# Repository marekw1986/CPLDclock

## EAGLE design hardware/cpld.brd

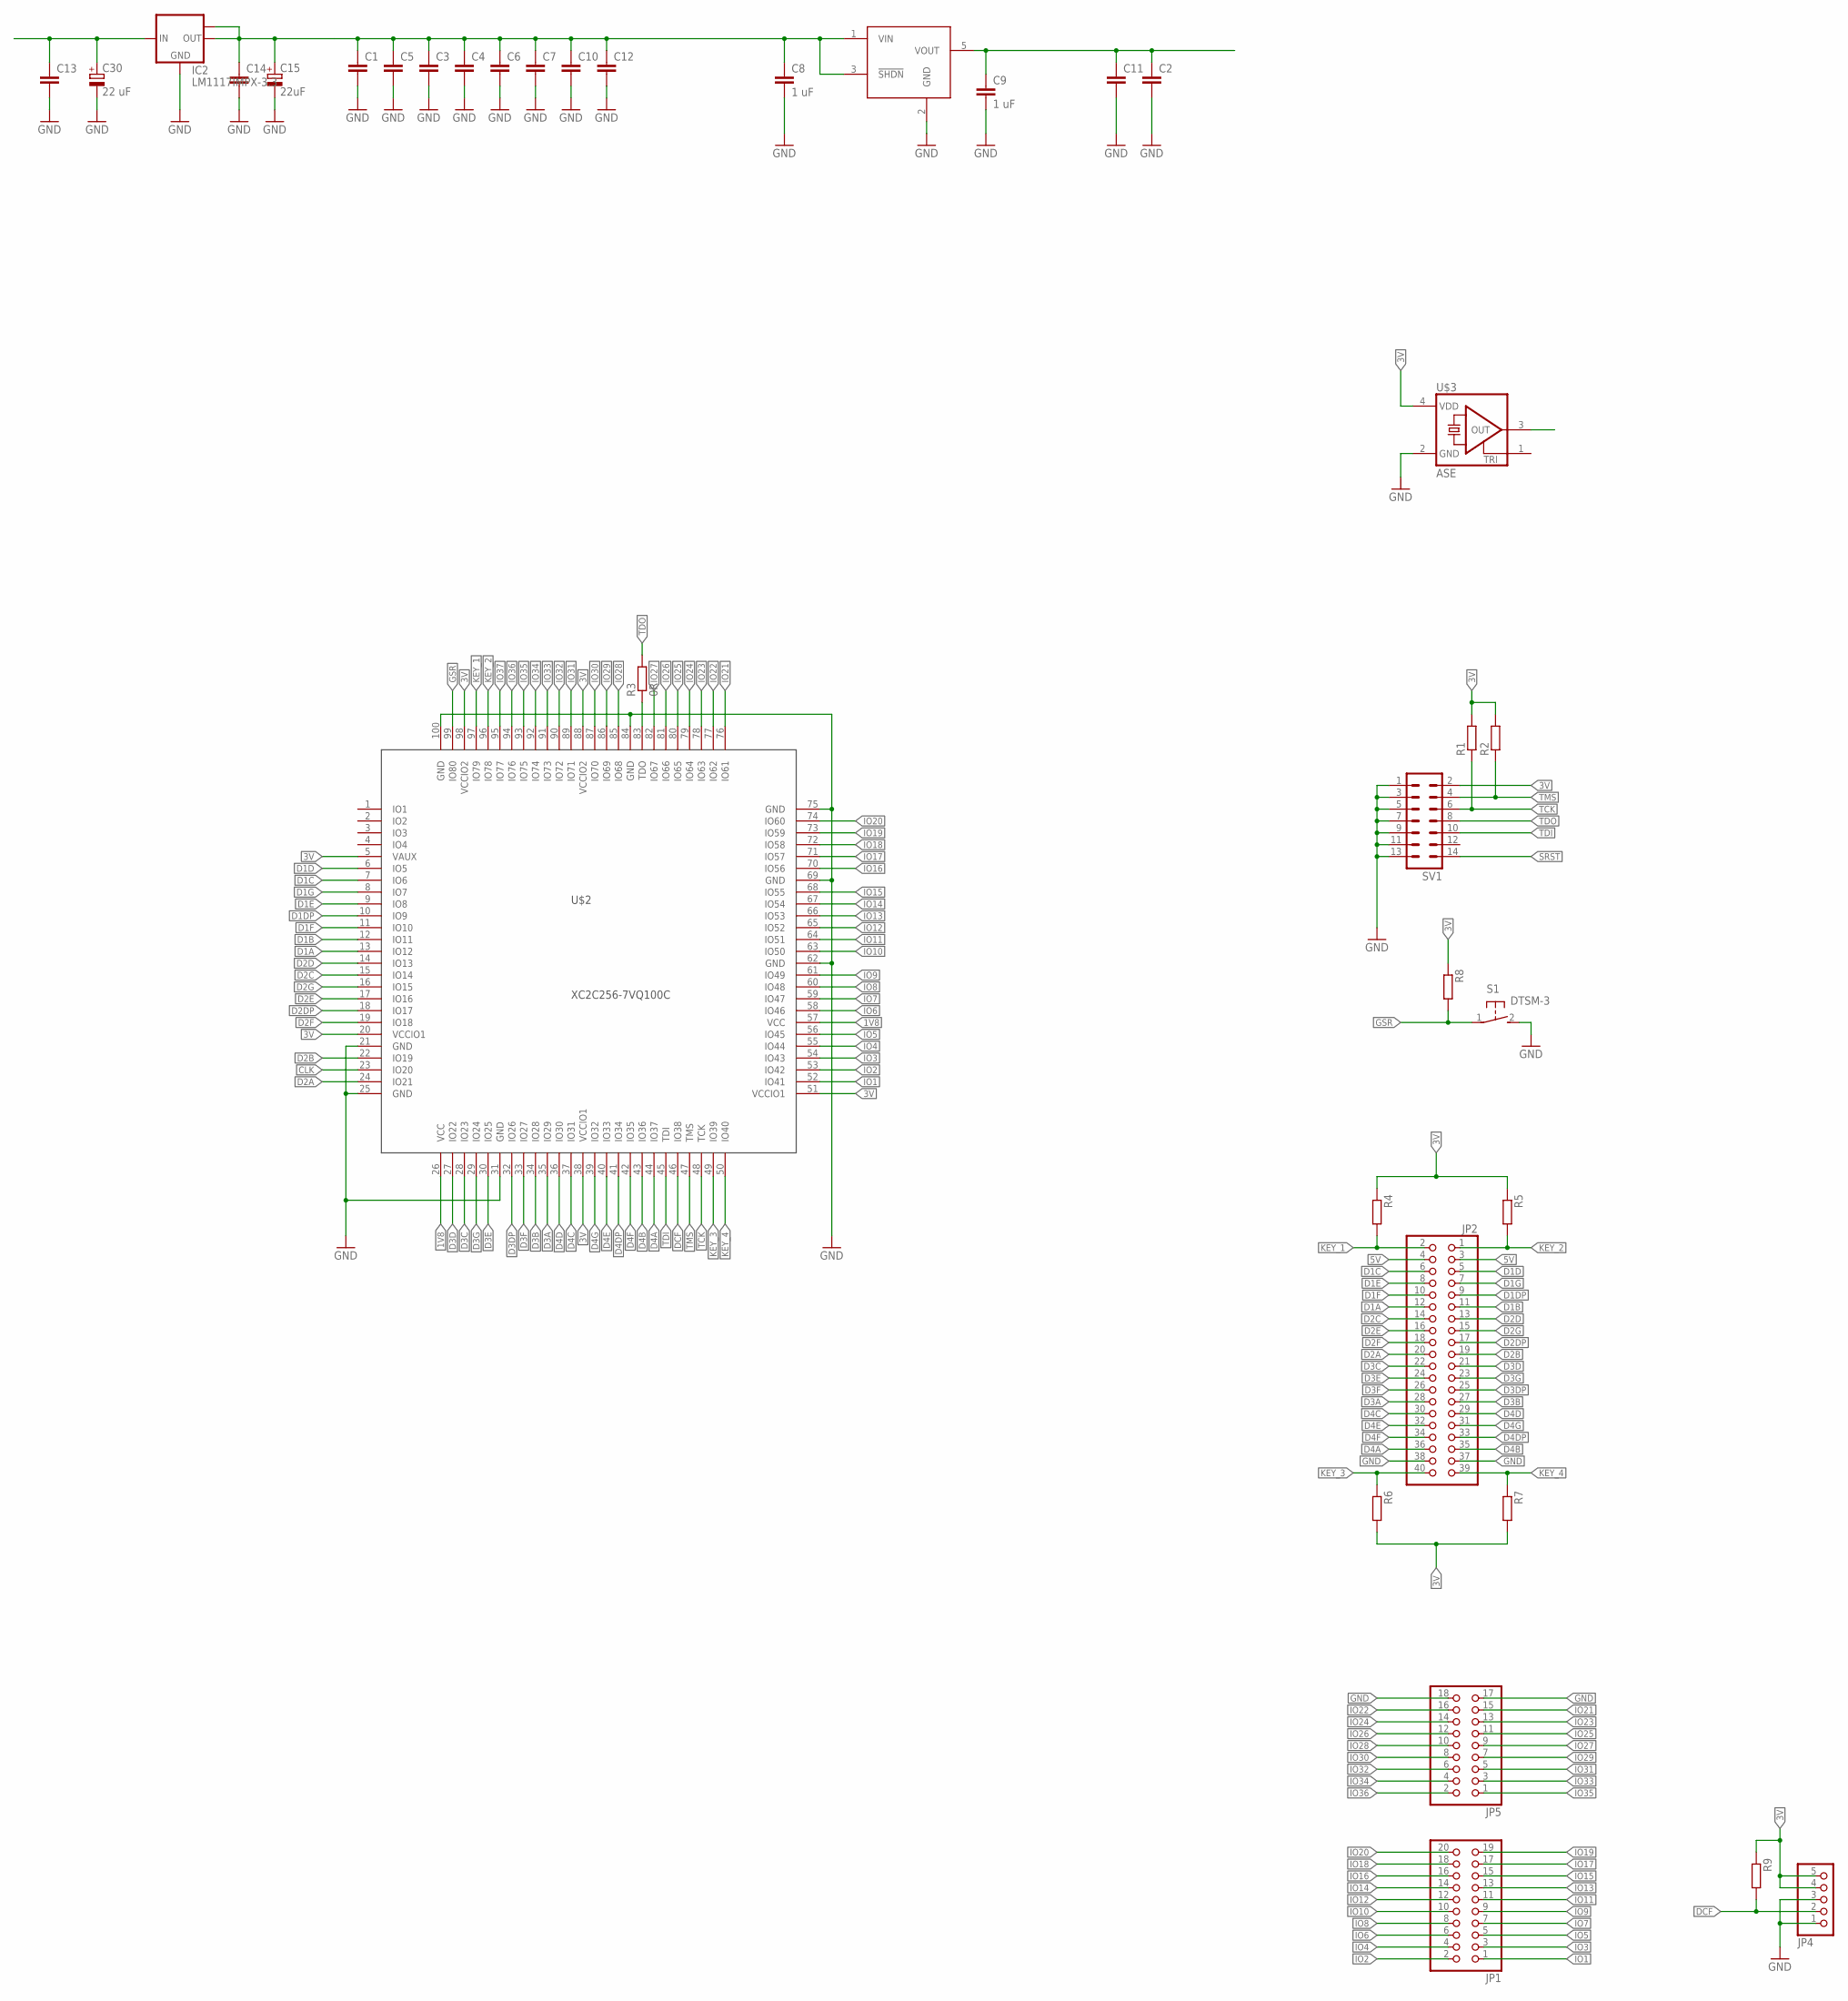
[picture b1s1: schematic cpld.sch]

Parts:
C1, C2, C4, C5, C7, C10, C11, C12, C13, C14: C-EUC0603; C0603
C3, C6: C-EUC0402; C0402
C8, C9: 1 uF; C0603
C15: 22uF; SMC_A
C30: 22 uF; SMC_A
IC2: LM1117IMPX-3.3; SOT223
JP1: PINHD-2X10; 2X10
JP2: PINHD-2X20_2.54-SMD; 2X20SMD
JP4: PINHD-1X5; 1X05
JP5: PINHD-2X9; 2X09
R1, R2, R4: R-EU_R0402; R0402
R3: 0R; R1206
R5, R6, R7, R8, R9: R-EU_R0603; R0603
S1: DTSM-3
SV1: ML14
U$1: MCP1802; SOT23-5
U$2: XC2C256-7VQ100C; TQFP100
U$3: ASE

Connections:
1V8: C2.1, C9.1, C11.1, U$1.5 (VOUT), U$2.26 (VCC), U$2.57 (VCC)
3V: C1.1, C3.1, C4.1, C5.1, C6.1, C7.1, C8.1, C10.1, C12.1, C14.1, C15.+, IC2.2 (OUT), IC2.TAB (OUT1), JP4.4, JP4.5, R1.2, R2.2, R4.1, R5.1, R6.2, R7.2, R8.1, R9.1, SV1.2, U$1.1 (VIN), U$1.3 (!SHDN), U$2.5 (VAUX), U$2.20 (VCCIO1), U$2.38 (VCCIO1), U$2.51 (VCCIO1), U$2.88 (VCCIO2), U$2.98 (VCCIO2), U$3.4 (VDD)
5V: C13.1, C30.+, IC2.3 (IN), JP2.3, JP2.4
CLK: U$2.23 (IO20), U$3.3 (OUT)
D1A: JP2.12, U$2.13 (IO12)
D1B: JP2.11, U$2.12 (IO11)
D1C: JP2.6, U$2.7 (IO6)
D1D: JP2.5, U$2.6 (IO5)
D1DP: JP2.9, U$2.10 (IO9)
D1E: JP2.8, U$2.9 (IO8)
D1F: JP2.10, U$2.11 (IO10)
D1G: JP2.7, U$2.8 (IO7)
D2A: JP2.20, U$2.24 (IO21)
D2B: JP2.19, U$2.22 (IO19)
D2C: JP2.14, U$2.15 (IO14)
D2D: JP2.13, U$2.14 (IO13)
D2DP: JP2.17, U$2.18 (IO17)
D2E: JP2.16, U$2.17 (IO16)
D2F: JP2.18, U$2.19 (IO18)
D2G: JP2.15, U$2.16 (IO15)
D3A: JP2.28, U$2.35 (IO29)
D3B: JP2.27, U$2.34 (IO28)
D3C: JP2.22, U$2.28 (IO23)
D3D: JP2.21, U$2.27 (IO22)
D3DP: JP2.25, U$2.32 (IO26)
D3E: JP2.24, U$2.30 (IO25)
D3F: JP2.26, U$2.33 (IO27)
D3G: JP2.23, U$2.29 (IO24)
D4A: JP2.36, U$2.44 (IO37)
D4B: JP2.35, U$2.43 (IO36)
D4C: JP2.30, U$2.37 (IO31)
D4D: JP2.29, U$2.36 (IO30)
D4DP: JP2.33, U$2.41 (IO34)
D4E: JP2.32, U$2.40 (IO33)
D4F: JP2.34, U$2.42 (IO35)
D4G: JP2.31, U$2.39 (IO32)
DCF: JP4.2, R9.2, U$2.46 (IO38)
GND: C1.2, C2.2, C3.2, C4.2, C5.2, C6.2, C7.2, C8.2, C9.2, C10.2, C11.2, C12.2, C13.2, C14.2, C15.-, C30.-, IC2.1 (GND), JP2.37, JP2.38, JP4.1, JP4.3, JP5.17, JP5.18, S1.2, SV1.1, SV1.3, SV1.5, SV1.7, SV1.9, SV1.11, SV1.13, U$1.2 (GND), U$2.21 (GND), U$2.25 (GND), U$2.31 (GND), U$2.62 (GND), U$2.69 (GND), U$2.75 (GND), U$2.84 (GND), U$2.100 (GND), U$3.2 (GND)
GSR: R8.2, S1.1, U$2.99 (IO80)
IO1: JP1.1, U$2.52 (IO41)
IO2: JP1.2, U$2.53 (IO42)
IO3: JP1.3, U$2.54 (IO43)
IO4: JP1.4, U$2.55 (IO44)
IO5: JP1.5, U$2.56 (IO45)
IO6: JP1.6, U$2.58 (IO46)
IO7: JP1.7, U$2.59 (IO47)
IO8: JP1.8, U$2.60 (IO48)
IO9: JP1.9, U$2.61 (IO49)
IO10: JP1.10, U$2.63 (IO50)
IO11: JP1.11, U$2.64 (IO51)
IO12: JP1.12, U$2.65 (IO52)
IO13: JP1.13, U$2.66 (IO53)
IO14: JP1.14, U$2.67 (IO54)
IO15: JP1.15, U$2.68 (IO55)
IO16: JP1.16, U$2.70 (IO56)
IO17: JP1.17, U$2.71 (IO57)
IO18: JP1.18, U$2.72 (IO58)
IO19: JP1.19, U$2.73 (IO59)
IO20: JP1.20, U$2.74 (IO60)
IO21: JP5.15, U$2.76 (IO61)
IO22: JP5.16, U$2.77 (IO62)
IO23: JP5.13, U$2.78 (IO63)
IO24: JP5.14, U$2.79 (IO64)
IO25: JP5.11, U$2.80 (IO65)
IO26: JP5.12, U$2.81 (IO66)
IO27: JP5.9, U$2.82 (IO67)
IO28: JP5.10, U$2.85 (IO68)
IO29: JP5.7, U$2.86 (IO69)
IO30: JP5.8, U$2.87 (IO70)
IO31: JP5.5, U$2.89 (IO71)
IO32: JP5.6, U$2.90 (IO72)
IO33: JP5.3, U$2.91 (IO73)
IO34: JP5.4, U$2.92 (IO74)
IO35: JP5.1, U$2.93 (IO75)
IO36: JP5.2, U$2.94 (IO76)
IO37: U$2.95 (IO77)
KEY_1: JP2.2, R4.2, U$2.97 (IO79)
KEY_2: JP2.1, R5.2, U$2.96 (IO78)
KEY_3: JP2.40, R6.1, U$2.49 (IO39)
KEY_4: JP2.39, R7.1, U$2.50 (IO40)
unnamed: R3.1, U$2.83 (TDO)
SRST: SV1.14
TCK: R1.1, SV1.6, U$2.48 (TCK)
TDI: SV1.10, U$2.45 (TDI)
TDO: R3.2, SV1.8
TMS: R2.1, SV1.4, U$2.47 (TMS)

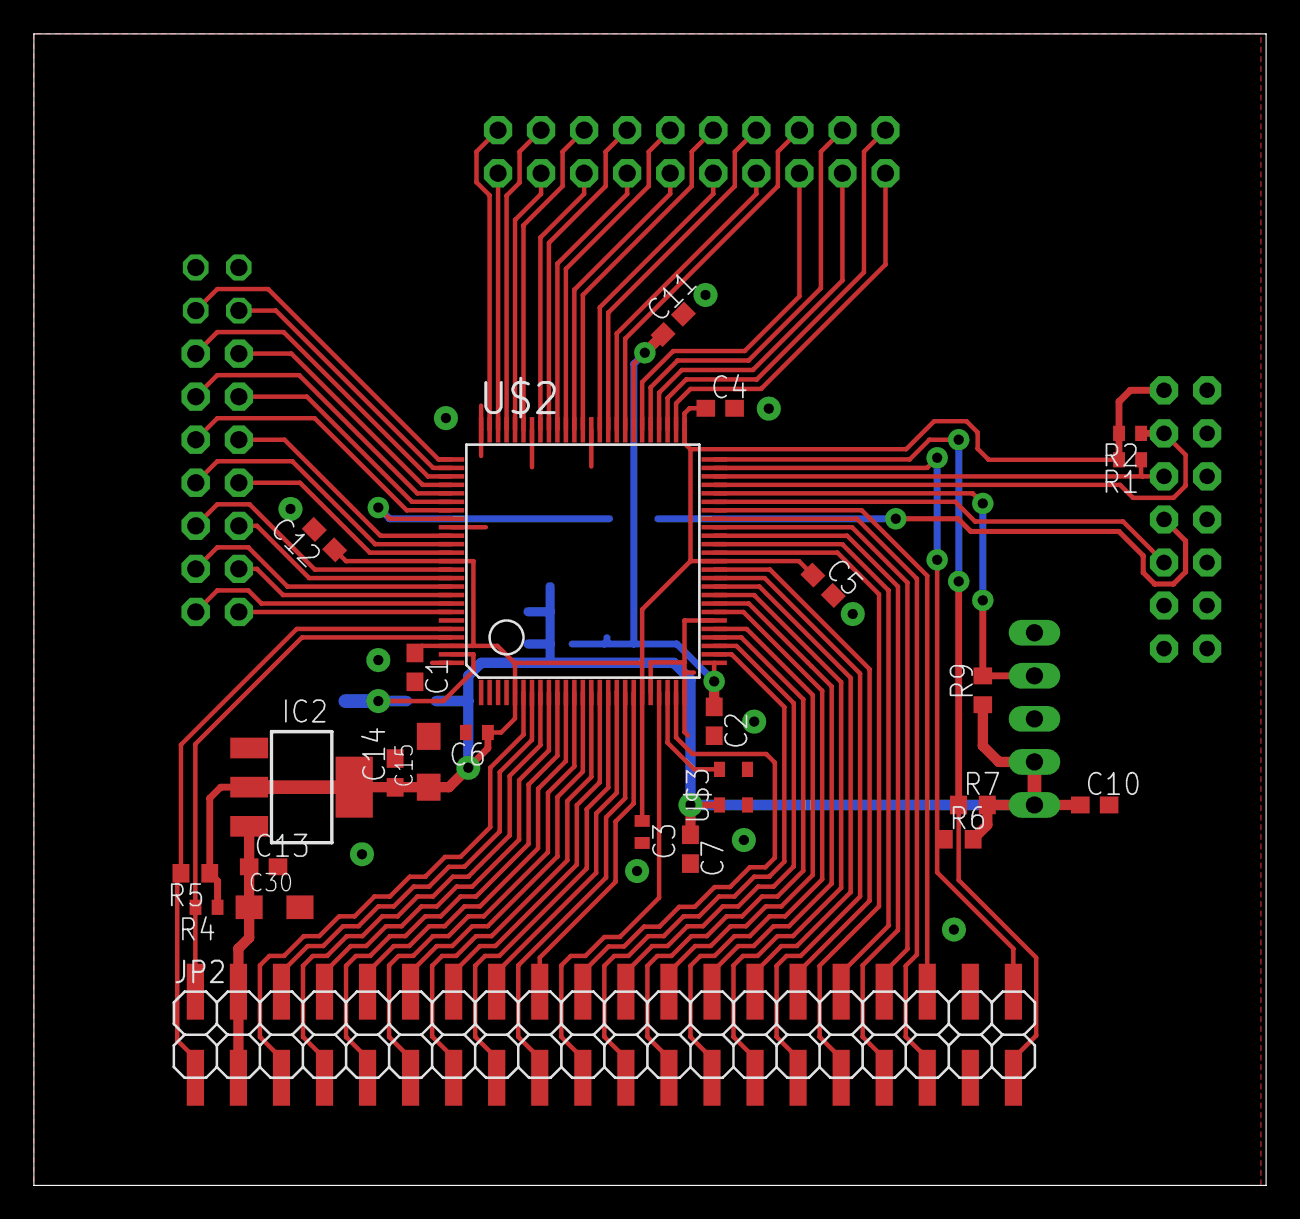
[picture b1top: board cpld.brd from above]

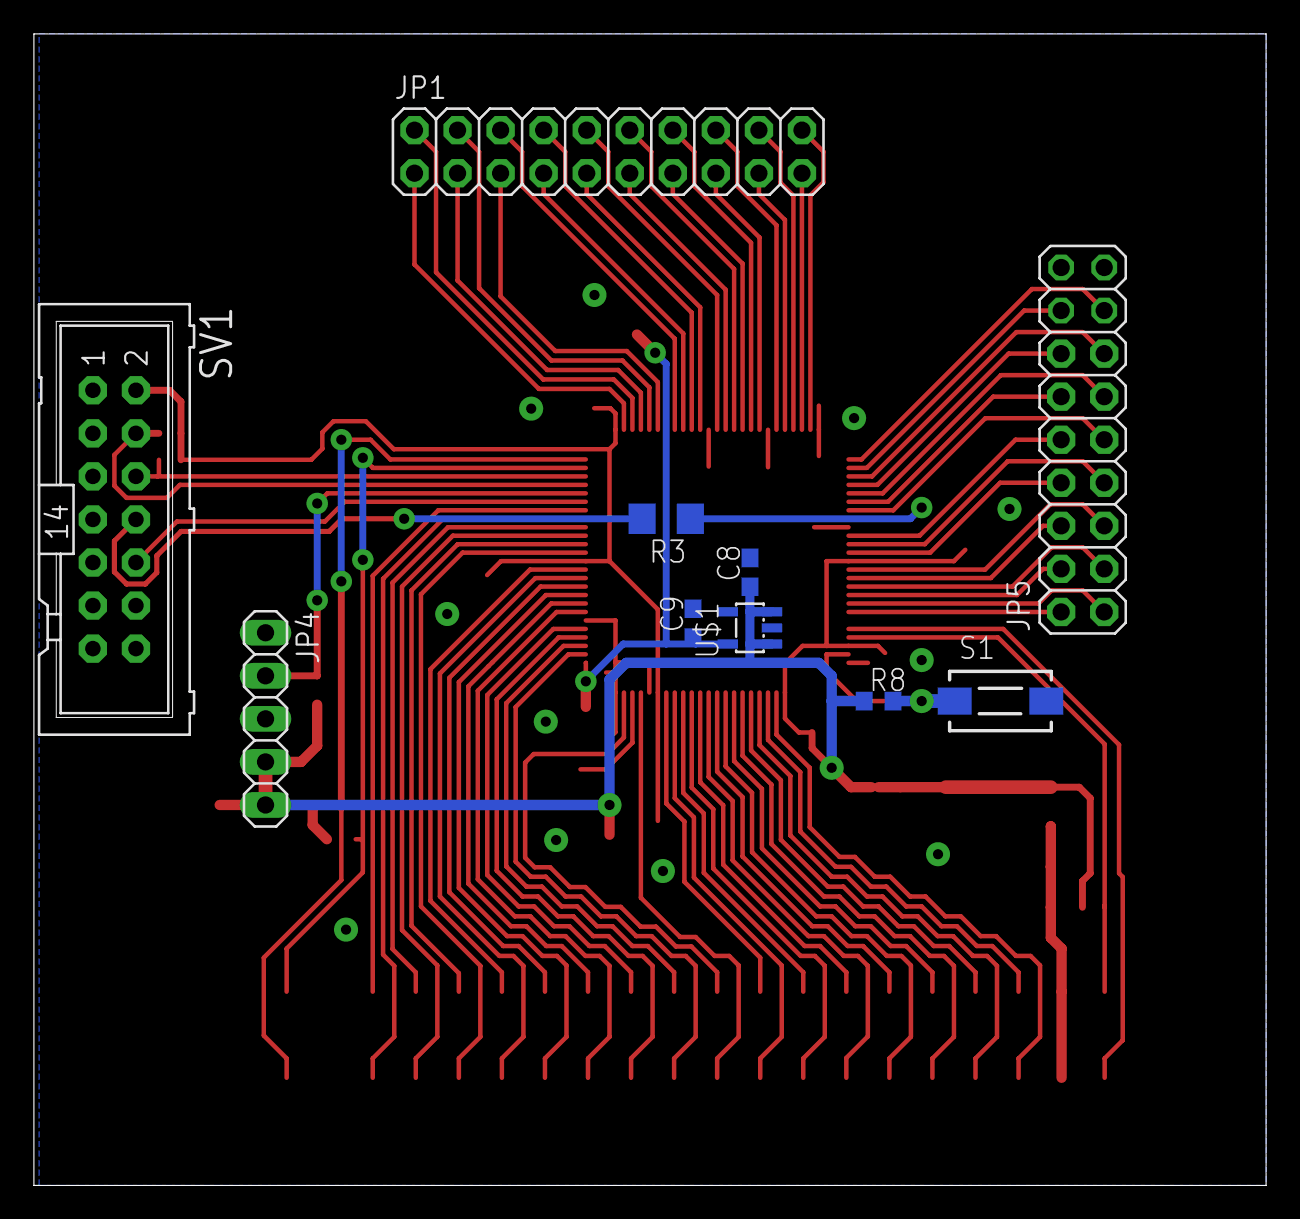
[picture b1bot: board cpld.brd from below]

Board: 2 copper layers, 72.7 x 67.9 mm, 35 parts (10 on the bottom side), 84 nets.

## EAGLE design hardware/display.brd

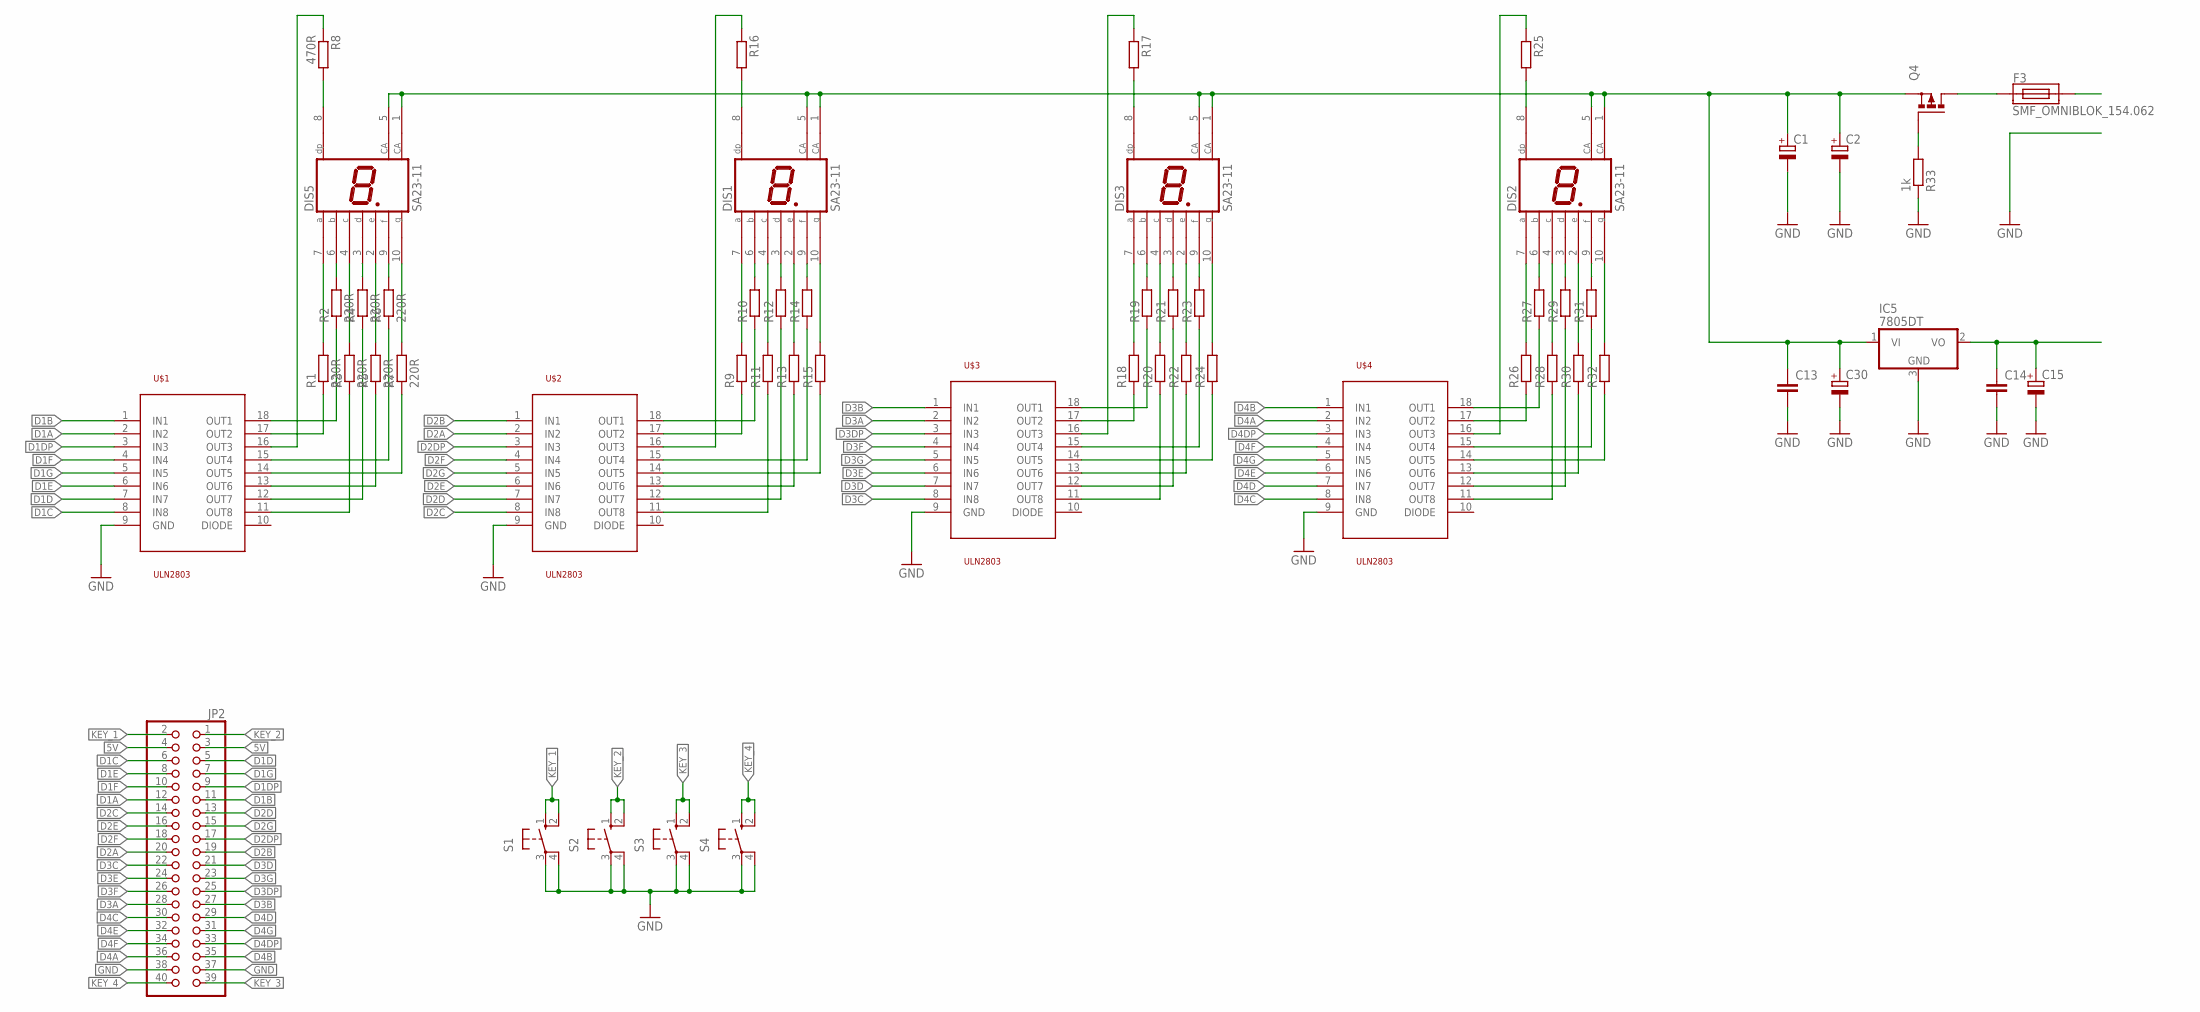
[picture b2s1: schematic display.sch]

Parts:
C1, C2: CPOL-EUSMCD; SMC_D
C13, C14: C-EUC0603; C0603
C15: CPOL-EUSMCB; SMC_B
C30: CPOL-EUSMCC; SMC_C
DIS1, DIS2, DIS3, DIS5: SA23-11; SX23-XX
F3: SMF_OMNIBLOK_154.062; NANO2_SMF_FUSEBLOCK
IC5: 7805DT; TO252
JP2: PINHD-2X20_2.54-SMD; 2X20SMD
Q4: P-MOSFET-SO8; SO-08
R1, R2, R3, R4, R5, R6, R7: 220R; R0603
R8: 470R; R0603
R9, R10, R11, R12, R13, R14, R15, R16, R17, R18, R19, R20, R21, R22, R23, R24, R25, R26, R27, R28, R29, R30, R31, R32: R-EU_R0603; R0603
R33: 1k; R0603
S1, S2, S3, S4: 40-XX; B3F-40XX
U$1, U$2, U$3, U$4: ULN2803; SO18L

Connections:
5V: C14.1, C15.+, IC5.2 (VO), JP2.3, JP2.4
9V: C1.+, C2.+, C13.1, C30.+, DIS1.1 (CA), DIS1.5 (CA), DIS2.1 (CA), DIS2.5 (CA), DIS3.1 (CA), DIS3.5 (CA), DIS5.1 (CA), DIS5.5 (CA), IC5.1 (VI), Q4.1 (S), Q4.2 (S), Q4.3 (S)
D1A: JP2.12, U$1.2 (IN2)
D1B: JP2.11, U$1.1 (IN1)
D1C: JP2.6, U$1.8 (IN8)
D1D: JP2.5, U$1.7 (IN7)
D1DP: JP2.9, U$1.3 (IN3)
D1E: JP2.8, U$1.6 (IN6)
D1F: JP2.10, U$1.4 (IN4)
D1G: JP2.7, U$1.5 (IN5)
D2A: JP2.20, U$2.2 (IN2)
D2B: JP2.19, U$2.1 (IN1)
D2C: JP2.14, U$2.8 (IN8)
D2D: JP2.13, U$2.7 (IN7)
D2DP: JP2.17, U$2.3 (IN3)
D2E: JP2.16, U$2.6 (IN6)
D2F: JP2.18, U$2.4 (IN4)
D2G: JP2.15, U$2.5 (IN5)
D3A: JP2.28, U$3.2 (IN2)
D3B: JP2.27, U$3.1 (IN1)
D3C: JP2.22, U$3.8 (IN8)
D3D: JP2.21, U$3.7 (IN7)
D3DP: JP2.25, U$3.3 (IN3)
D3E: JP2.24, U$3.6 (IN6)
D3F: JP2.26, U$3.4 (IN4)
D3G: JP2.23, U$3.5 (IN5)
D4A: JP2.36, U$4.2 (IN2)
D4B: JP2.35, U$4.1 (IN1)
D4C: JP2.30, U$4.8 (IN8)
D4D: JP2.29, U$4.7 (IN7)
D4DP: JP2.33, U$4.3 (IN3)
D4E: JP2.32, U$4.6 (IN6)
D4F: JP2.34, U$4.4 (IN4)
D4G: JP2.31, U$4.5 (IN5)
GND: C1.-, C2.-, C13.2, C14.2, C15.-, C30.-, IC5.3 (GND), JP2.37, JP2.38, R33.1, S1.3, S1.4 (P1), S2.3, S2.4 (P1), S3.3, S3.4 (P1), S4.3, S4.4 (P1), U$1.9 (GND), U$2.9 (GND), U$3.9 (GND), U$4.9 (GND)
KEY_1: JP2.2, S1.1 (S), S1.2 (S1)
KEY_2: JP2.1, S2.1 (S), S2.2 (S1)
KEY_3: JP2.39, S3.1 (S), S3.2 (S1)
KEY_4: JP2.40, S4.1 (S), S4.2 (S1)
unnamed: DIS5.7 (A), R1.2
unnamed: DIS5.6 (B), R2.2
unnamed: Q4.4 (G), R33.2
unnamed: DIS5.4 (C), R3.2
unnamed: DIS5.3 (D), R4.2
unnamed: DIS5.2 (E), R5.2
unnamed: DIS5.9 (F), R6.2
unnamed: DIS5.10 (G), R7.2
unnamed: DIS5.8 (DP), R8.2
unnamed: DIS1.7 (A), R9.2
unnamed: DIS1.4 (C), R11.2
unnamed: DIS1.2 (E), R13.2
unnamed: DIS1.10 (G), R15.2
unnamed: DIS1.6 (B), R10.2
unnamed: DIS1.3 (D), R12.2
unnamed: DIS1.9 (F), R14.2
unnamed: DIS1.8 (DP), R16.2
unnamed: DIS3.8 (DP), R17.2
unnamed: DIS3.7 (A), R18.2
unnamed: DIS3.4 (C), R20.2
unnamed: DIS3.2 (E), R22.2
unnamed: DIS3.10 (G), R24.2
unnamed: DIS3.6 (B), R19.2
unnamed: DIS3.3 (D), R21.2
unnamed: DIS3.9 (F), R23.2
unnamed: DIS2.8 (DP), R25.2
unnamed: DIS2.7 (A), R26.2
unnamed: DIS2.4 (C), R28.2
unnamed: DIS2.2 (E), R30.2
unnamed: F3.1, Q4.5 (D), Q4.6 (D), Q4.7 (D), Q4.8 (D)
unnamed: DIS2.10 (G), R32.2
unnamed: DIS2.6 (B), R27.2
unnamed: DIS2.3 (D), R29.2
unnamed: DIS2.9 (F), R31.2
unnamed: R5.1, U$1.13 (OUT6)
unnamed: R4.1, U$1.12 (OUT7)
unnamed: R3.1, U$1.11 (OUT8)
unnamed: R7.1, U$1.14 (OUT5)
unnamed: R6.1, U$1.15 (OUT4)
unnamed: R8.1, U$1.16 (OUT3)
unnamed: R1.1, U$1.17 (OUT2)
unnamed: R2.1, U$1.18 (OUT1)
unnamed: R15.1, U$2.14 (OUT5)
unnamed: R14.1, U$2.15 (OUT4)
unnamed: R16.1, U$2.16 (OUT3)
unnamed: R9.1, U$2.17 (OUT2)
unnamed: R10.1, U$2.18 (OUT1)
unnamed: R11.1, U$2.11 (OUT8)
unnamed: R12.1, U$2.12 (OUT7)
unnamed: R13.1, U$2.13 (OUT6)
unnamed: R24.1, U$3.14 (OUT5)
unnamed: R23.1, U$3.15 (OUT4)
unnamed: R17.1, U$3.16 (OUT3)
unnamed: R18.1, U$3.17 (OUT2)
unnamed: R19.1, U$3.18 (OUT1)
unnamed: R20.1, U$3.11 (OUT8)
unnamed: R21.1, U$3.12 (OUT7)
unnamed: R22.1, U$3.13 (OUT6)
unnamed: R32.1, U$4.14 (OUT5)
unnamed: R31.1, U$4.15 (OUT4)
unnamed: R25.1, U$4.16 (OUT3)
unnamed: R26.1, U$4.17 (OUT2)
unnamed: R27.1, U$4.18 (OUT1)
unnamed: R28.1, U$4.11 (OUT8)
unnamed: R29.1, U$4.12 (OUT7)
unnamed: R30.1, U$4.13 (OUT6)

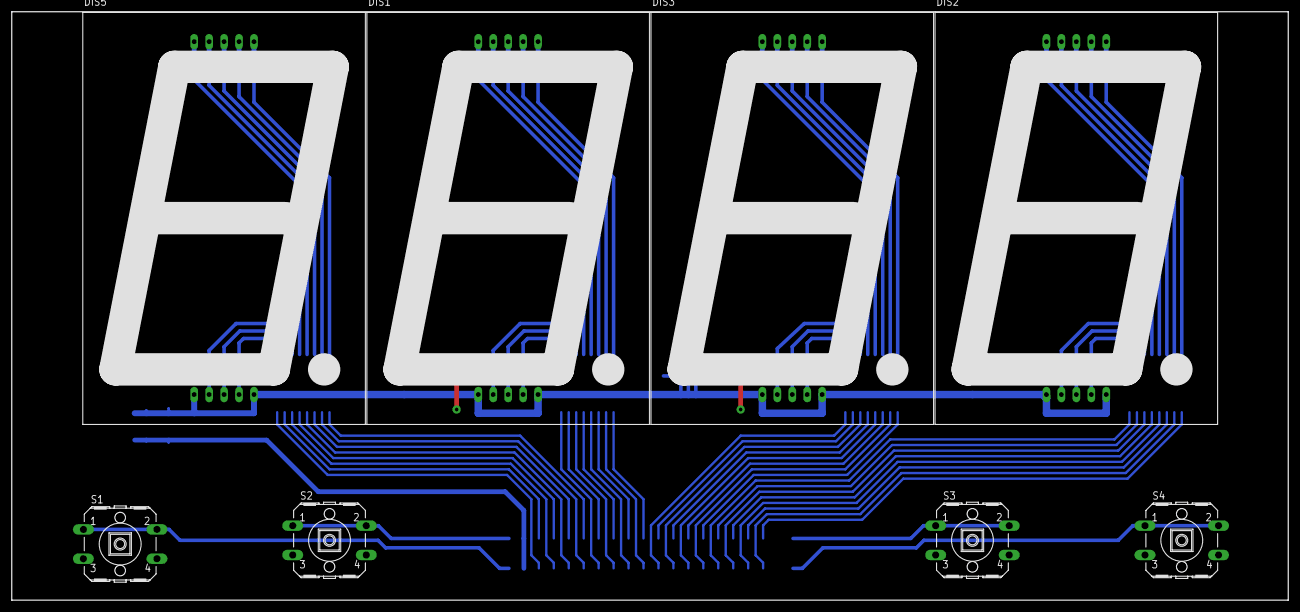
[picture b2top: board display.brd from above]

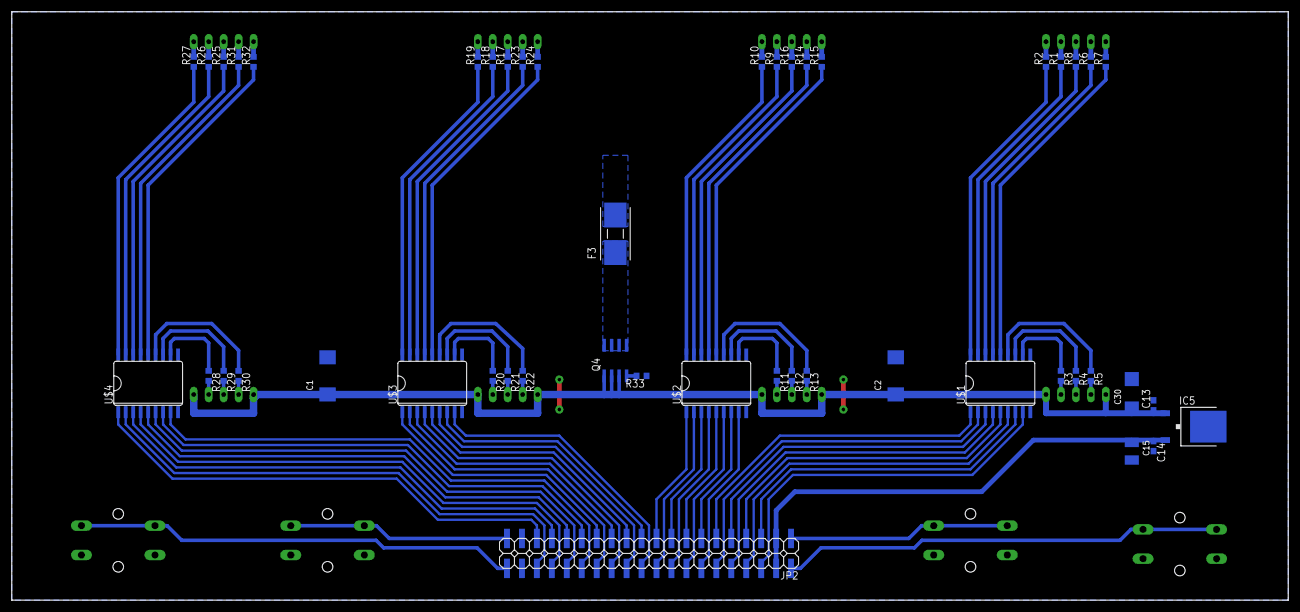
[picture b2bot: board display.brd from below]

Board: 2 copper layers, 216.8 x 99.9 mm, 55 parts (47 on the bottom side), 105 nets.

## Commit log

2020-10-28 Board updated
2020-10-29 Boards updated
2020-11-17 Hardware project updates and fixes
2020-12-04 Code added
2020-12-05 code updated
2020-12-07 switching to seconds display
2020-12-07 Clock is working
2020-12-11 Optimized
2021-03-11 Some changes
2022-12-07 Moved project to xc2c256

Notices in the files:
parts and their libraries:
SparkFun-Aesthetics: Licensing: Creative Commons ShareAlike 4.0 International - https://creativecommons.org/licenses/by-sa/4.0
SparkFun: Licensing: CC v3.0 Share-Alike You are welcome to use this library for commercial purposes.
